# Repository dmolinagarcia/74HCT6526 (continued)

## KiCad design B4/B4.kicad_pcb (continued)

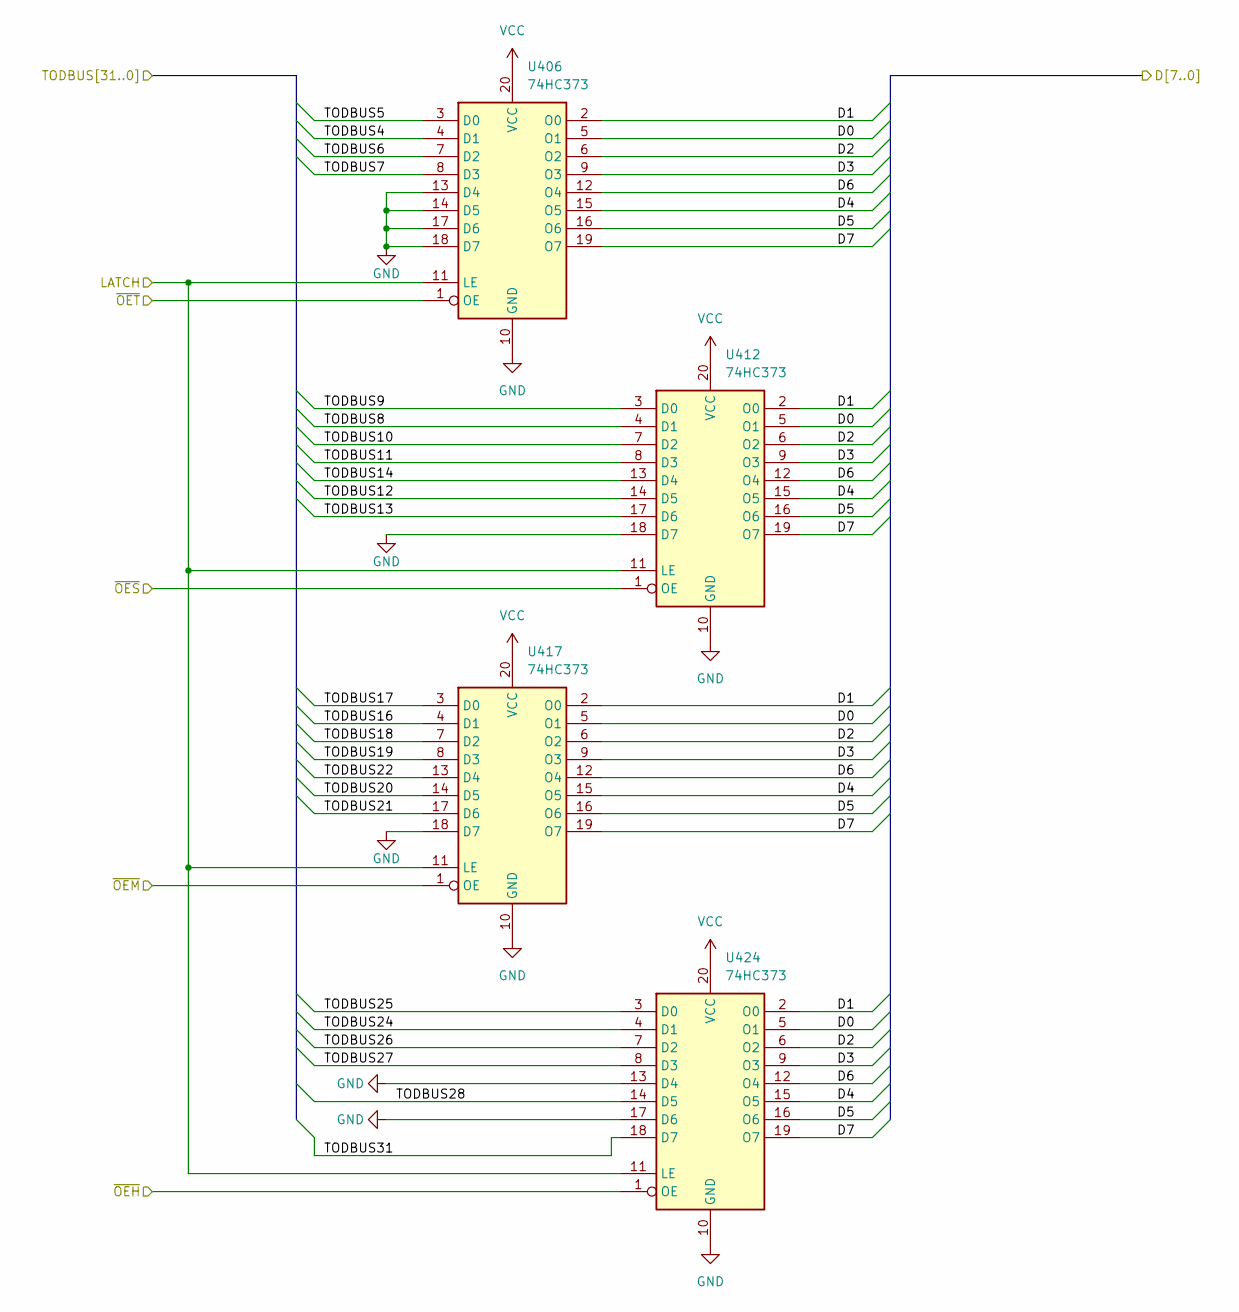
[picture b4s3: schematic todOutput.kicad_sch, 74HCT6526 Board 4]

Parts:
U406, U412, U417, U424: 74HC373; SOIC-20W_7.5x12.8mm_P1.27mm

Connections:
/todComparator/TODBUS4: U406.4 (D1); also elsewhere on the board
/todComparator/TODBUS5: U406.3 (D0); also elsewhere on the board
/todComparator/TODBUS6: U406.7 (D2); also elsewhere on the board
/todComparator/TODBUS7: U406.8 (D3); also elsewhere on the board
/todComparator/TODBUS8: U412.4 (D1); also elsewhere on the board
/todComparator/TODBUS9: U412.3 (D0); also elsewhere on the board
/todComparator/TODBUS10: U412.7 (D2); also elsewhere on the board
/todComparator/TODBUS11: U412.8 (D3); also elsewhere on the board
/todComparator/TODBUS12: U412.14 (D5); also elsewhere on the board
/todComparator/TODBUS13: U412.17 (D6); also elsewhere on the board
/todComparator/TODBUS14: U412.13 (D4); also elsewhere on the board
/todComparator/TODBUS16: U417.4 (D1); also elsewhere on the board
/todComparator/TODBUS17: U417.3 (D0); also elsewhere on the board
/todComparator/TODBUS18: U417.7 (D2); also elsewhere on the board
/todComparator/TODBUS19: U417.8 (D3); also elsewhere on the board
/todComparator/TODBUS20: U417.14 (D5); also elsewhere on the board
/todComparator/TODBUS21: U417.17 (D6); also elsewhere on the board
/todComparator/TODBUS22: U417.13 (D4); also elsewhere on the board
/todComparator/TODBUS24: U424.4 (D1); also elsewhere on the board
/todComparator/TODBUS25: U424.3 (D0); also elsewhere on the board
/todComparator/TODBUS26: U424.7 (D2); also elsewhere on the board
/todComparator/TODBUS27: U424.8 (D3); also elsewhere on the board
/todComparator/TODBUS28: U424.14 (D5); also elsewhere on the board
/todComparator/TODBUS31: U424.18 (D7); also elsewhere on the board
/todControl/LATCH: U406.11 (LE), U412.11 (LE), U417.11 (LE), U424.11 (LE); also elsewhere on the board
/todControl/~OEH: U424.1 (OE); also elsewhere on the board
/todControl/~OEM: U417.1 (OE); also elsewhere on the board
/todControl/~OES: U412.1 (OE); also elsewhere on the board
/todControl/~OET: U406.1 (OE); also elsewhere on the board
D0: U406.5 (O1), U412.5 (O1), U417.5 (O1), U424.5 (O1); also elsewhere on the board
D1: U406.2 (O0), U412.2 (O0), U417.2 (O0), U424.2 (O0); also elsewhere on the board
D2: U406.6 (O2), U412.6 (O2), U417.6 (O2), U424.6 (O2); also elsewhere on the board
D3: U406.9 (O3), U412.9 (O3), U417.9 (O3), U424.9 (O3); also elsewhere on the board
D4: U406.15 (O5), U412.15 (O5), U417.15 (O5), U424.15 (O5); also elsewhere on the board
D5: U406.16 (O6), U412.16 (O6), U417.16 (O6), U424.16 (O6); also elsewhere on the board
D6: U406.12 (O4), U412.12 (O4), U417.12 (O4), U424.12 (O4); also elsewhere on the board
D7: U406.19 (O7), U412.19 (O7), U417.19 (O7), U424.19 (O7); also elsewhere on the board
GND: U406.10 (GND), U406.13 (D4), U406.14 (D5), U406.17 (D6), U406.18 (D7), U412.10 (GND), U412.18 (D7), U417.10 (GND), U417.18 (D7), U424.10 (GND), U424.13 (D4), U424.17 (D6); also elsewhere on the board
VCC: U406.20 (VCC), U412.20 (VCC), U417.20 (VCC), U424.20 (VCC); also elsewhere on the board

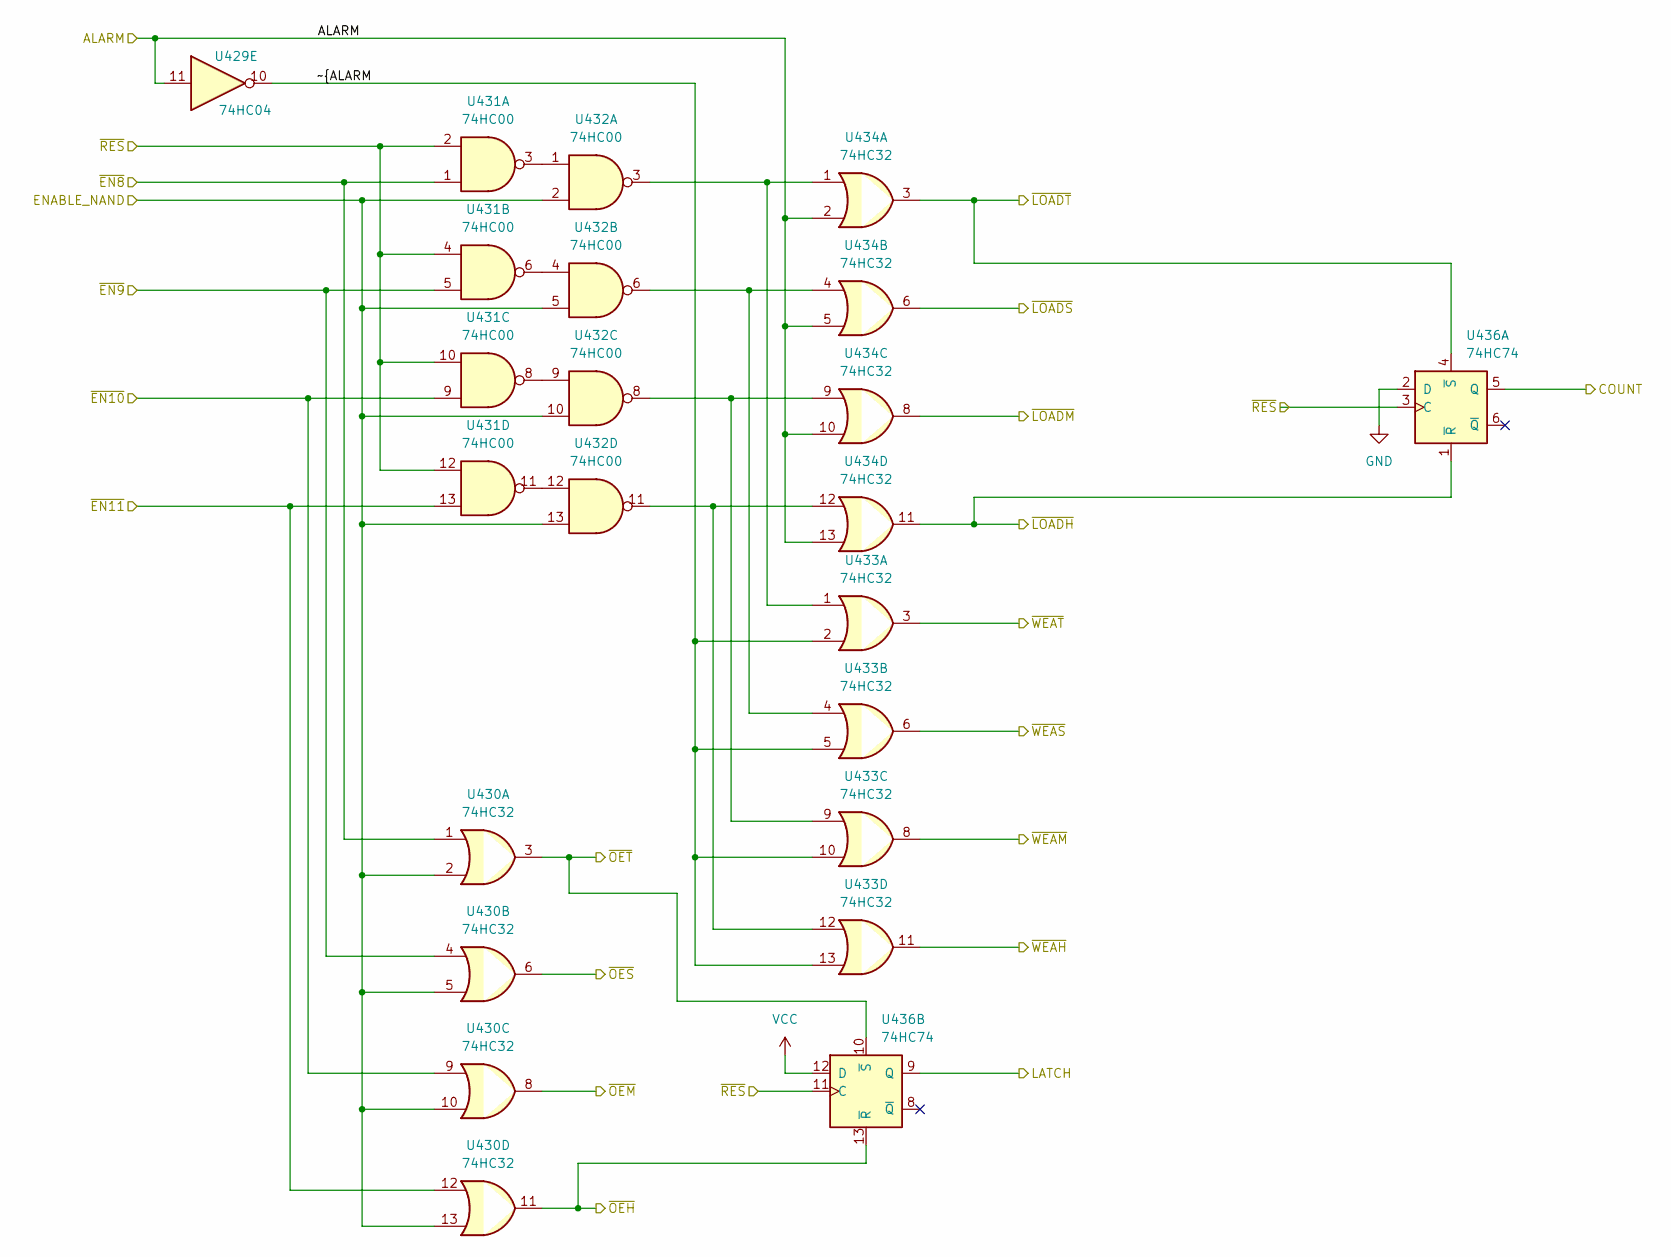
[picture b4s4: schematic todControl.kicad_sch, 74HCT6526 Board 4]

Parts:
U429: 74HC04; SOIC-14_3.9x8.7mm_P1.27mm
U430, U433, U434: 74HC32; SOIC-14_3.9x8.7mm_P1.27mm
U431, U432: 74HC00; SOIC-14_3.9x8.7mm_P1.27mm
U436: 74HC74; SOIC-14_3.9x8.7mm_P1.27mm

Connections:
/todAlarm/~WEAH: U433.11; also elsewhere on the board
/todAlarm/~WEAM: U433.8; also elsewhere on the board
/todAlarm/~WEAS: U433.6; also elsewhere on the board
/todAlarm/~WEAT: U433.3; also elsewhere on the board
/todControl/COUNT: U436.5 (Q); also elsewhere on the board
/todControl/LATCH: U436.9 (Q); also elsewhere on the board
/todControl/~ALARM: U429.10, U433.2, U433.5, U433.10, U433.13
/todControl/~LOADH: U434.11, U436.1 (~R); also elsewhere on the board
/todControl/~LOADM: U434.8; also elsewhere on the board
/todControl/~LOADS: U434.6; also elsewhere on the board
/todControl/~LOADT: U434.3, U436.4 (~S); also elsewhere on the board
/todControl/~OEH: U430.11, U436.13 (~R); also elsewhere on the board
/todControl/~OEM: U430.8; also elsewhere on the board
/todControl/~OES: U430.6; also elsewhere on the board
/todControl/~OET: U430.3, U436.10 (~S); also elsewhere on the board
ALARM: U429.11, U434.2, U434.5, U434.10, U434.13; also elsewhere on the board
ENABLE_NAND: U430.2, U430.5, U430.10, U430.13, U432.2, U432.5, U432.10, U432.13; also elsewhere on the board
GND: U436.2 (D); also elsewhere on the board
unnamed: U431.3, U432.1
unnamed: U431.6, U432.4
unnamed: U431.8, U432.9
unnamed: U431.11, U432.12
unnamed: U432.3, U433.1, U434.1
unnamed: U432.6, U433.4, U434.4
unnamed: U432.8, U433.9, U434.9
unnamed: U432.11, U433.12, U434.12
VCC: U436.12 (D); also elsewhere on the board
~EN8: U430.1, U431.1; also elsewhere on the board
~EN9: U430.4, U431.5; also elsewhere on the board
~EN10: U430.9, U431.9; also elsewhere on the board
~EN11: U430.12, U431.13; also elsewhere on the board
~RES: U431.2, U431.4, U431.10, U431.12, U436.3 (C), U436.11 (C); also elsewhere on the board

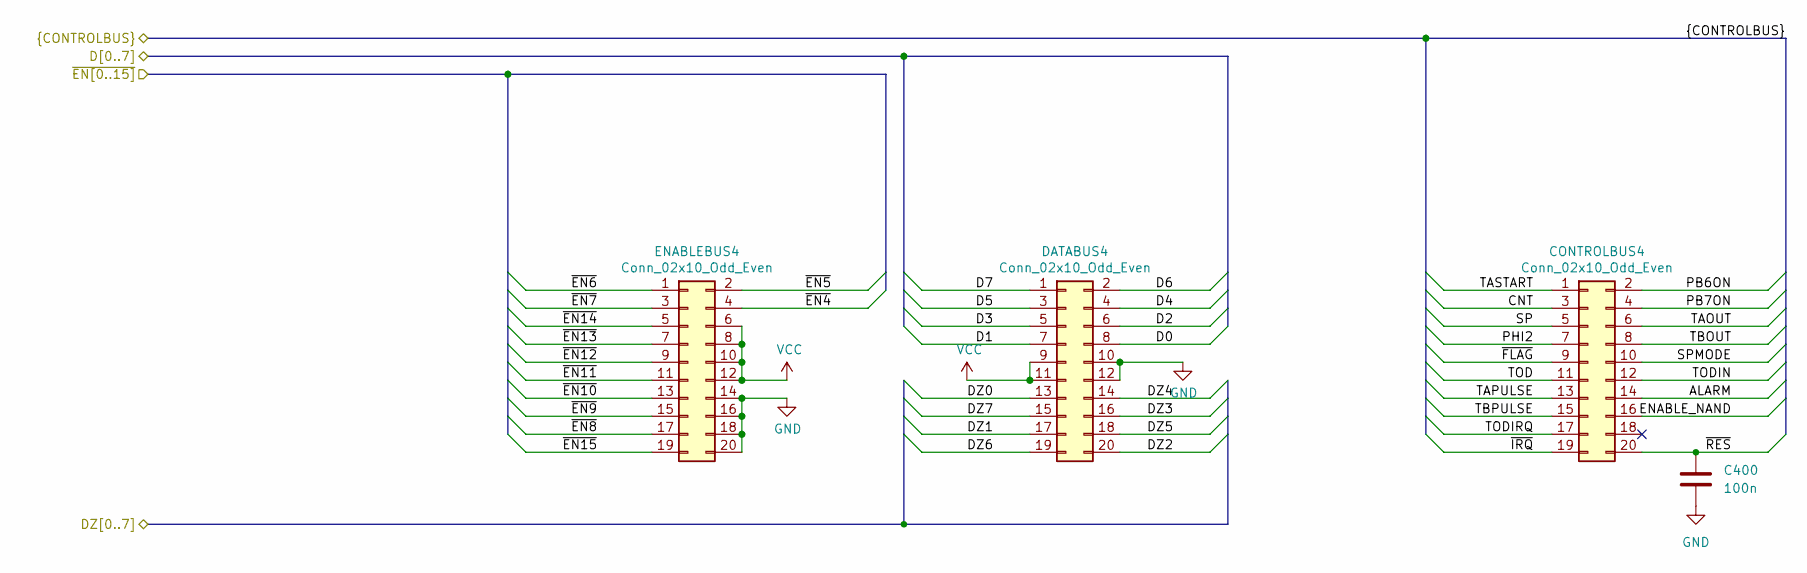
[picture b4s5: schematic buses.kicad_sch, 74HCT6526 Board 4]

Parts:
C400: 100n; C_0603_1608Metric
CONTROLBUS4: Conn_02x10_Odd_Even; PinHeader_2x10_P2.54mm_Vertical
DATABUS4: Conn_02x10_Odd_Even; PinHeader_2x10_P2.54mm_Vertical
ENABLEBUS4: Conn_02x10_Odd_Even; PinHeader_2x10_P2.54mm_Vertical

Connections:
ALARM: CONTROLBUS4.14; also elsewhere on the board
CNT: CONTROLBUS4.3
D0: DATABUS4.8; also elsewhere on the board
D1: DATABUS4.7; also elsewhere on the board
D2: DATABUS4.6; also elsewhere on the board
D3: DATABUS4.5; also elsewhere on the board
D4: DATABUS4.4; also elsewhere on the board
D5: DATABUS4.3; also elsewhere on the board
D6: DATABUS4.2; also elsewhere on the board
D7: DATABUS4.1; also elsewhere on the board
DZ0: DATABUS4.13; also elsewhere on the board
DZ1: DATABUS4.17; also elsewhere on the board
DZ2: DATABUS4.20; also elsewhere on the board
DZ3: DATABUS4.16; also elsewhere on the board
DZ4: DATABUS4.14; also elsewhere on the board
DZ5: DATABUS4.18; also elsewhere on the board
DZ6: DATABUS4.19; also elsewhere on the board
DZ7: DATABUS4.15; also elsewhere on the board
ENABLE_NAND: CONTROLBUS4.16; also elsewhere on the board
GND: C400.2, DATABUS4.10, DATABUS4.12, ENABLEBUS4.14, ENABLEBUS4.16, ENABLEBUS4.18, ENABLEBUS4.20; also elsewhere on the board
PB6ON: CONTROLBUS4.2
PB7ON: CONTROLBUS4.4
PHI2: CONTROLBUS4.7; also elsewhere on the board
SP: CONTROLBUS4.5
SPMODE: CONTROLBUS4.10
TAOUT: CONTROLBUS4.6
TAPULSE: CONTROLBUS4.13
TASTART: CONTROLBUS4.1
TBOUT: CONTROLBUS4.8
TBPULSE: CONTROLBUS4.15
TOD: CONTROLBUS4.11; also elsewhere on the board
TODIN: CONTROLBUS4.12; also elsewhere on the board
TODIRQ: CONTROLBUS4.17; also elsewhere on the board
VCC: DATABUS4.9, DATABUS4.11, ENABLEBUS4.6, ENABLEBUS4.8, ENABLEBUS4.10, ENABLEBUS4.12; also elsewhere on the board
~EN4: ENABLEBUS4.4
~EN5: ENABLEBUS4.2
~EN6: ENABLEBUS4.1
~EN7: ENABLEBUS4.3
~EN8: ENABLEBUS4.17; also elsewhere on the board
~EN9: ENABLEBUS4.15; also elsewhere on the board
~EN10: ENABLEBUS4.13; also elsewhere on the board
~EN11: ENABLEBUS4.11; also elsewhere on the board
~EN12: ENABLEBUS4.9
~EN13: ENABLEBUS4.7
~EN14: ENABLEBUS4.5
~EN15: ENABLEBUS4.19
~FLAG: CONTROLBUS4.9
~IRQ: CONTROLBUS4.19
~RES: C400.1, CONTROLBUS4.20; also elsewhere on the board

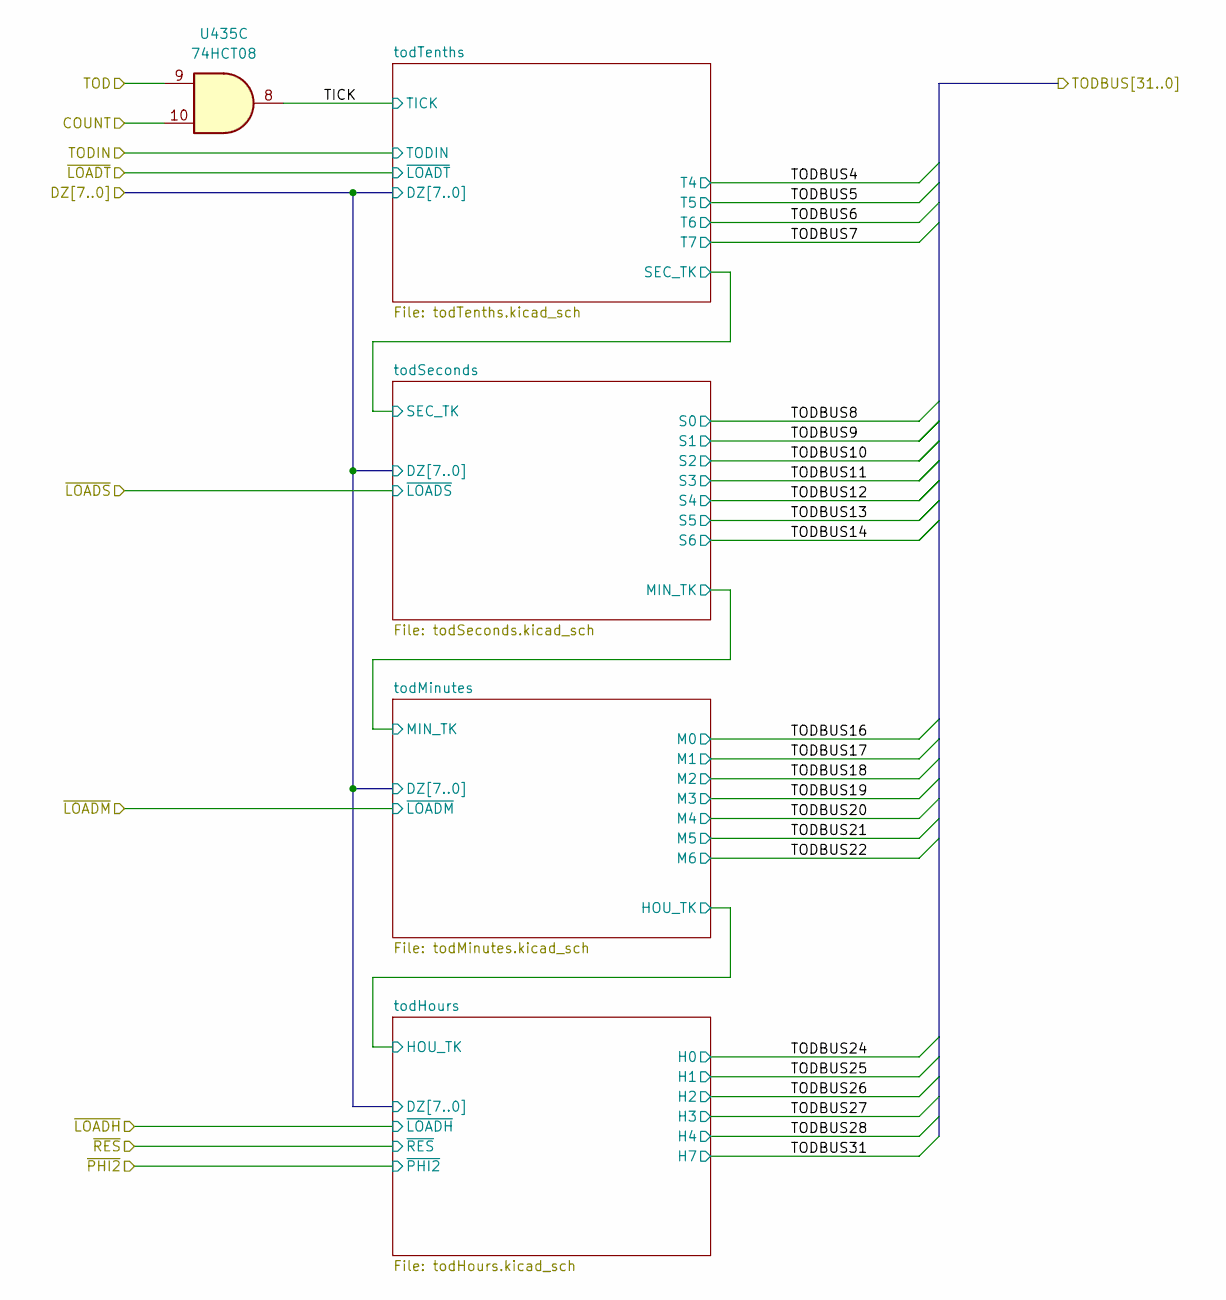
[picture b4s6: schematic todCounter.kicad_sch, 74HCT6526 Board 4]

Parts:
U435: 74HCT08; SOIC-14_3.9x8.7mm_P1.27mm

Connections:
/todControl/COUNT: U435.10; also elsewhere on the board
/todCounter/TICK: U435.8; also elsewhere on the board
TOD: U435.9; also elsewhere on the board

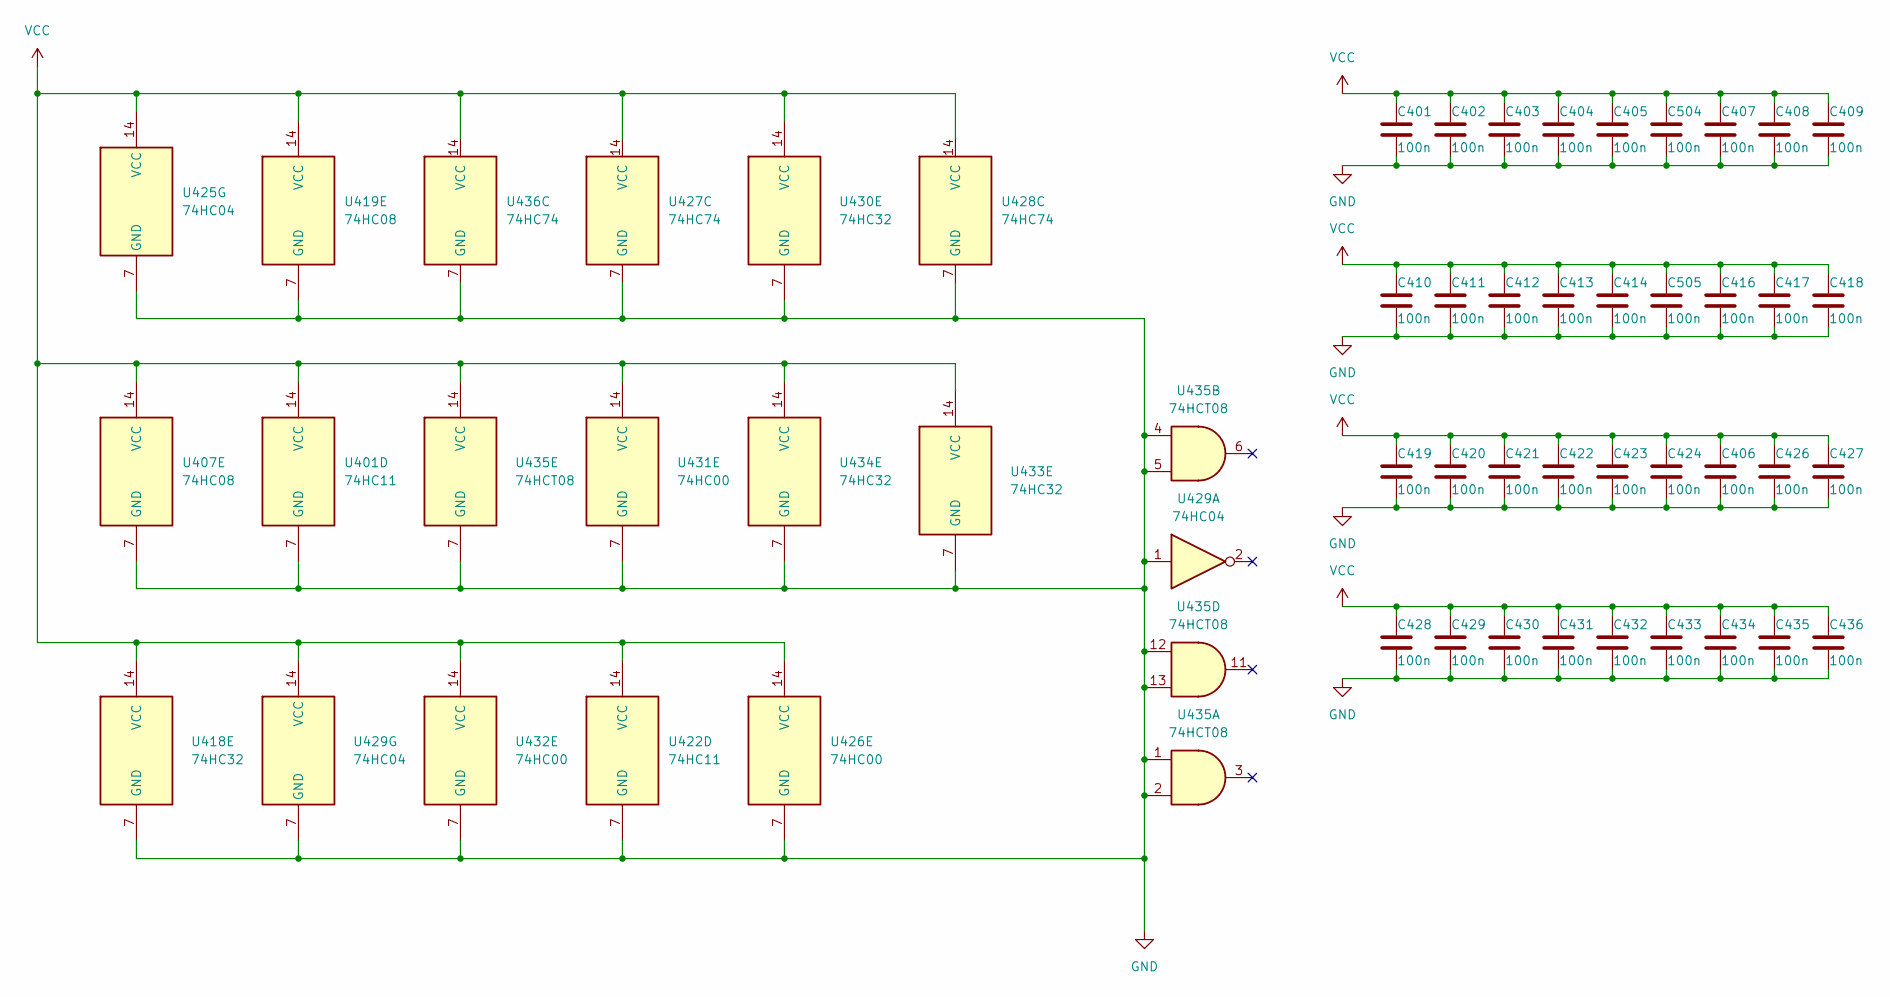
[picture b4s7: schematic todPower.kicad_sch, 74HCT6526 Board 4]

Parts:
C401, C402, C403, C404, C405, C406, C407, C408, C409, C410, C411, C412, C413, C414, C416, C417, C418, C419, C420, C421, C422, C423, C424, C426, C427, C428, C429, C430, C431, C432, C433, C434, C435, C436, C504, C505: 100n; C_0603_1608Metric
U401, U422: 74HC11; SOIC-14_3.9x8.7mm_P1.27mm
U407, U419: 74HC08; SOIC-14_3.9x8.7mm_P1.27mm
U418, U430, U433, U434: 74HC32; SOIC-14_3.9x8.7mm_P1.27mm
U425, U429: 74HC04; SOIC-14_3.9x8.7mm_P1.27mm
U426, U431, U432: 74HC00; SOIC-14_3.9x8.7mm_P1.27mm
U427, U428, U436: 74HC74; SOIC-14_3.9x8.7mm_P1.27mm
U435: 74HCT08; SOIC-14_3.9x8.7mm_P1.27mm

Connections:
GND: C401.2, C402.2, C403.2, C404.2, C405.2, C406.2, C407.2, C408.2, C409.2, C410.2, C411.2, C412.2, C413.2, C414.2, C416.2, C417.2, C418.2, C419.2, C420.2, C421.2, C422.2, C423.2, C424.2, C426.2, C427.2, C428.2, C429.2, C430.2, C431.2, C432.2, C433.2, C434.2, C435.2, C436.2, C504.2, C505.2, U401.7 (GND), U407.7 (GND), U418.7 (GND), U419.7 (GND), U422.7 (GND), U425.7 (GND), U426.7 (GND), U427.7 (GND), U428.7 (GND), U429.1, U429.7 (GND), U430.7 (GND), U431.7 (GND), U432.7 (GND), U433.7 (GND), U434.7 (GND), U435.1, U435.2, U435.4, U435.5, U435.7 (GND), U435.12, U435.13, U436.7 (GND); also elsewhere on the board
VCC: C401.1, C402.1, C403.1, C404.1, C405.1, C406.1, C407.1, C408.1, C409.1, C410.1, C411.1, C412.1, C413.1, C414.1, C416.1, C417.1, C418.1, C419.1, C420.1, C421.1, C422.1, C423.1, C424.1, C426.1, C427.1, C428.1, C429.1, C430.1, C431.1, C432.1, C433.1, C434.1, C435.1, C436.1, C504.1, C505.1, U401.14 (VCC), U407.14 (VCC), U418.14 (VCC), U419.14 (VCC), U422.14 (VCC), U425.14 (VCC), U426.14 (VCC), U427.14 (VCC), U428.14 (VCC), U429.14 (VCC), U430.14 (VCC), U431.14 (VCC), U432.14 (VCC), U433.14 (VCC), U434.14 (VCC), U435.14 (VCC), U436.14 (VCC); also elsewhere on the board

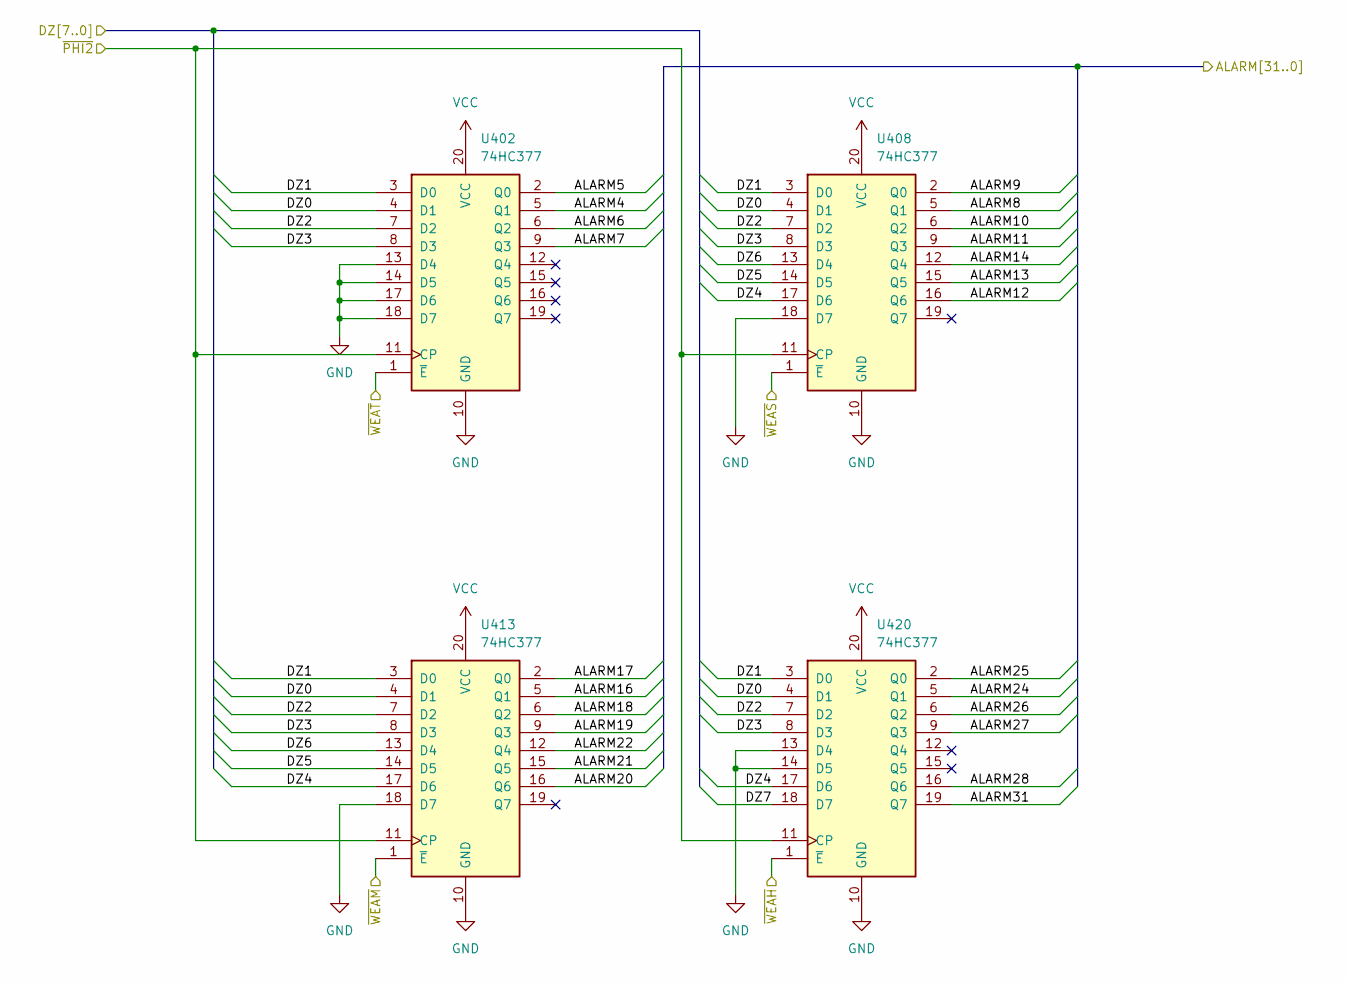
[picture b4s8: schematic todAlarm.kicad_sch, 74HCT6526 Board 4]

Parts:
U402, U408, U413, U420: 74HC377; SOIC-20W_7.5x12.8mm_P1.27mm

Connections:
/todAlarm/ALARM4: U402.5 (Q1); also elsewhere on the board
/todAlarm/ALARM5: U402.2 (Q0); also elsewhere on the board
/todAlarm/ALARM6: U402.6 (Q2); also elsewhere on the board
/todAlarm/ALARM7: U402.9 (Q3); also elsewhere on the board
/todAlarm/ALARM8: U408.5 (Q1); also elsewhere on the board
/todAlarm/ALARM9: U408.2 (Q0); also elsewhere on the board
/todAlarm/ALARM10: U408.6 (Q2); also elsewhere on the board
/todAlarm/ALARM11: U408.9 (Q3); also elsewhere on the board
/todAlarm/ALARM12: U408.16 (Q6); also elsewhere on the board
/todAlarm/ALARM13: U408.15 (Q5); also elsewhere on the board
/todAlarm/ALARM14: U408.12 (Q4); also elsewhere on the board
/todAlarm/ALARM16: U413.5 (Q1); also elsewhere on the board
/todAlarm/ALARM17: U413.2 (Q0); also elsewhere on the board
/todAlarm/ALARM18: U413.6 (Q2); also elsewhere on the board
/todAlarm/ALARM19: U413.9 (Q3); also elsewhere on the board
/todAlarm/ALARM20: U413.16 (Q6); also elsewhere on the board
/todAlarm/ALARM21: U413.15 (Q5); also elsewhere on the board
/todAlarm/ALARM22: U413.12 (Q4); also elsewhere on the board
/todAlarm/ALARM24: U420.5 (Q1); also elsewhere on the board
/todAlarm/ALARM25: U420.2 (Q0); also elsewhere on the board
/todAlarm/ALARM26: U420.6 (Q2); also elsewhere on the board
/todAlarm/ALARM27: U420.9 (Q3); also elsewhere on the board
/todAlarm/ALARM28: U420.16 (Q6); also elsewhere on the board
/todAlarm/ALARM31: U420.19 (Q7); also elsewhere on the board
/todAlarm/~WEAH: U420.1 (~E); also elsewhere on the board
/todAlarm/~WEAM: U413.1 (~E); also elsewhere on the board
/todAlarm/~WEAS: U408.1 (~E); also elsewhere on the board
/todAlarm/~WEAT: U402.1 (~E); also elsewhere on the board
/~PHI2: U402.11 (CP), U408.11 (CP), U413.11 (CP), U420.11 (CP); also elsewhere on the board
DZ0: U402.4 (D1), U408.4 (D1), U413.4 (D1), U420.4 (D1); also elsewhere on the board
DZ1: U402.3 (D0), U408.3 (D0), U413.3 (D0), U420.3 (D0); also elsewhere on the board
DZ2: U402.7 (D2), U408.7 (D2), U413.7 (D2), U420.7 (D2); also elsewhere on the board
DZ3: U402.8 (D3), U408.8 (D3), U413.8 (D3), U420.8 (D3); also elsewhere on the board
DZ4: U408.17 (D6), U413.17 (D6), U420.17 (D6); also elsewhere on the board
DZ5: U408.14 (D5), U413.14 (D5); also elsewhere on the board
DZ6: U408.13 (D4), U413.13 (D4); also elsewhere on the board
DZ7: U420.18 (D7); also elsewhere on the board
GND: U402.10 (GND), U402.13 (D4), U402.14 (D5), U402.17 (D6), U402.18 (D7), U408.10 (GND), U408.18 (D7), U413.10 (GND), U413.18 (D7), U420.10 (GND), U420.13 (D4), U420.14 (D5); also elsewhere on the board
VCC: U402.20 (VCC), U408.20 (VCC), U413.20 (VCC), U420.20 (VCC); also elsewhere on the board

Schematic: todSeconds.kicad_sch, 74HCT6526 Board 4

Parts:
U407: 74HC08; SOIC-14_3.9x8.7mm_P1.27mm
U409, U410: 74HC193; SOIC-16_3.9x9.9mm_P1.27mm

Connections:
/todComparator/TODBUS8: U410.3 (QA); also elsewhere on the board
/todComparator/TODBUS9: U407.13, U410.2 (QB); also elsewhere on the board
/todComparator/TODBUS10: U410.6 (QC); also elsewhere on the board
/todComparator/TODBUS11: U407.12, U410.7 (QD); also elsewhere on the board
/todComparator/TODBUS12: U409.3 (QA); also elsewhere on the board
/todComparator/TODBUS13: U407.1, U409.2 (QB); also elsewhere on the board
/todComparator/TODBUS14: U407.2, U409.6 (QC); also elsewhere on the board
/todControl/~LOADS: U409.11 (~LOAD), U410.11 (~LOAD); also elsewhere on the board
/todCounter/todMinutes/MIN_TK: U407.3, U409.14 (CLR); also elsewhere on the board
/todCounter/todSeconds/SEC_TK: U410.5 (UP); also elsewhere on the board
DZ0: U410.15 (A); also elsewhere on the board
DZ1: U410.1 (B); also elsewhere on the board
DZ2: U410.10 (C); also elsewhere on the board
DZ3: U410.9 (D); also elsewhere on the board
DZ4: U409.15 (A); also elsewhere on the board
DZ5: U409.1 (B); also elsewhere on the board
DZ6: U409.10 (C); also elsewhere on the board
GND: U409.8 (GND), U409.9 (D), U410.8 (GND); also elsewhere on the board
unnamed: U407.11, U409.5 (UP), U410.14 (CLR)
VCC: U409.4 (DOWN), U409.16 (VCC), U410.4 (DOWN), U410.16 (VCC); also elsewhere on the board

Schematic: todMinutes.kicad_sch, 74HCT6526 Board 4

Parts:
U407: 74HC08; SOIC-14_3.9x8.7mm_P1.27mm
U414, U415: 74HC193; SOIC-16_3.9x9.9mm_P1.27mm

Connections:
/todComparator/TODBUS16: U415.3 (QA); also elsewhere on the board
/todComparator/TODBUS17: U407.4, U415.2 (QB); also elsewhere on the board
/todComparator/TODBUS18: U415.6 (QC); also elsewhere on the board
/todComparator/TODBUS19: U407.5, U415.7 (QD); also elsewhere on the board
/todComparator/TODBUS20: U414.3 (QA); also elsewhere on the board
/todComparator/TODBUS21: U407.10, U414.2 (QB); also elsewhere on the board
/todComparator/TODBUS22: U407.9, U414.6 (QC); also elsewhere on the board
/todControl/~LOADM: U414.11 (~LOAD), U415.11 (~LOAD); also elsewhere on the board
/todCounter/todHours/HOU_TK: U407.8, U414.14 (CLR); also elsewhere on the board
/todCounter/todMinutes/MIN_TK: U415.5 (UP); also elsewhere on the board
DZ0: U415.15 (A); also elsewhere on the board
DZ1: U415.1 (B); also elsewhere on the board
DZ2: U415.10 (C); also elsewhere on the board
DZ3: U415.9 (D); also elsewhere on the board
DZ4: U414.15 (A); also elsewhere on the board
DZ5: U414.1 (B); also elsewhere on the board
DZ6: U414.10 (C); also elsewhere on the board
GND: U414.8 (GND), U414.9 (D), U415.8 (GND); also elsewhere on the board
unnamed: U407.6, U414.5 (UP), U415.14 (CLR)
VCC: U414.4 (DOWN), U414.16 (VCC), U415.4 (DOWN), U415.16 (VCC); also elsewhere on the board

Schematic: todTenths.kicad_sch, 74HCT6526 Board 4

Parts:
U401: 74HC11; SOIC-14_3.9x8.7mm_P1.27mm
U403, U404: 74HC193; SOIC-16_3.9x9.9mm_P1.27mm
U418: 74HC32; SOIC-14_3.9x8.7mm_P1.27mm
U429: 74HC04; SOIC-14_3.9x8.7mm_P1.27mm

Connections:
/todComparator/TODBUS4: U404.3 (QA); also elsewhere on the board
/todComparator/TODBUS5: U401.3, U401.4, U404.2 (QB); also elsewhere on the board
/todComparator/TODBUS6: U404.6 (QC); also elsewhere on the board
/todComparator/TODBUS7: U401.5, U404.7 (QD); also elsewhere on the board
/todControl/~LOADT: U403.11 (~LOAD), U404.11 (~LOAD); also elsewhere on the board
/todCounter/TICK: U403.5 (UP); also elsewhere on the board
/todCounter/todSeconds/SEC_TK: U401.6, U404.14 (CLR); also elsewhere on the board
/todCounter/todTenths/TODBUS0: U401.10, U403.3 (QA)
/todCounter/todTenths/TODBUS1: U401.13, U403.2 (QB)
/todCounter/todTenths/TODBUS2: U401.2, U401.9, U403.6 (QC)
DZ0: U404.15 (A); also elsewhere on the board
DZ1: U404.1 (B); also elsewhere on the board
DZ2: U404.10 (C); also elsewhere on the board
DZ3: U404.9 (D); also elsewhere on the board
GND: U403.1 (B), U403.8 (GND), U403.9 (D), U403.10 (C), U403.15 (A), U404.8 (GND); also elsewhere on the board
unnamed: U401.1, U429.6
unnamed: U401.8, U418.2
unnamed: U401.12, U418.1
unnamed: U403.14 (CLR), U404.5 (UP), U418.3
TODIN: U401.11, U429.5; also elsewhere on the board
VCC: U403.4 (DOWN), U403.16 (VCC), U404.4 (DOWN), U404.16 (VCC); also elsewhere on the board

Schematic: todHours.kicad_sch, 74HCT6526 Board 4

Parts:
U418: 74HC32; SOIC-14_3.9x8.7mm_P1.27mm
U419: 74HC08; SOIC-14_3.9x8.7mm_P1.27mm
U421: 74HC193; SOIC-16_3.9x9.9mm_P1.27mm
U422: 74HC11; SOIC-14_3.9x8.7mm_P1.27mm
U425, U429: 74HC04; SOIC-14_3.9x8.7mm_P1.27mm
U426: 74HC00; SOIC-14_3.9x8.7mm_P1.27mm
U427, U428: 74HC74; SOIC-14_3.9x8.7mm_P1.27mm

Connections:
/todComparator/TODBUS24: U421.3 (QA), U422.4; also elsewhere on the board
/todComparator/TODBUS25: U421.2 (QB), U422.1, U422.5, U422.11; also elsewhere on the board
/todComparator/TODBUS26: U421.6 (QC); also elsewhere on the board
/todComparator/TODBUS27: U421.7 (QD), U422.2, U425.11; also elsewhere on the board
/todComparator/TODBUS28: U422.3, U422.10, U427.5 (Q); also elsewhere on the board
/todComparator/TODBUS31: U427.9 (Q); also elsewhere on the board
/todControl/~LOADH: U418.4, U419.13; also elsewhere on the board
/todCounter/todHours/H4_FLIP: U418.8, U427.3 (C)
/todCounter/todHours/H7_FLIP: U427.11 (C), U428.9 (Q)
/todCounter/todHours/HOU_TK: U421.5 (UP); also elsewhere on the board
/todCounter/todHours/~H4: U422.13, U427.2 (D), U427.6 (~Q)
/~PHI2: U428.3 (C), U428.11 (C); also elsewhere on the board
DZ0: U418.13; also elsewhere on the board
DZ1: U419.2; also elsewhere on the board
DZ2: U419.4; also elsewhere on the board
DZ3: U419.10; also elsewhere on the board
DZ4: U425.5, U426.5; also elsewhere on the board
DZ7: U425.9, U426.9; also elsewhere on the board
GND: U421.8 (GND), U428.12 (D); also elsewhere on the board
unnamed: U418.5, U425.2
unnamed: U418.9, U421.14 (CLR), U422.12
unnamed: U418.10, U422.6, U425.13
unnamed: U418.11, U421.15 (A)
unnamed: U418.6, U418.12, U425.3
unnamed: U419.1, U419.5, U419.9, U425.4, U426.1, U426.4, U426.10, U426.13
unnamed: U419.3, U421.1 (B)
unnamed: U419.6, U421.10 (C)
unnamed: U419.8, U421.9 (D)
unnamed: U419.11, U421.11 (~LOAD)
unnamed: U419.12, U428.5 (Q)
unnamed: U422.8, U429.3
unnamed: U422.9, U425.10
unnamed: U425.6, U426.2
unnamed: U425.8, U426.12
unnamed: U425.12, U428.1 (~R)
unnamed: U426.3, U427.1 (~R)
unnamed: U426.6, U427.4 (~S)
unnamed: U426.8, U427.10 (~S)
unnamed: U426.11, U427.13 (~R)
unnamed: U427.8 (~Q), U427.12 (D)
unnamed: U428.13 (~R), U429.4
VCC: U421.4 (DOWN), U421.16 (VCC), U428.2 (D), U428.4 (~S), U428.10 (~S); also elsewhere on the board
~RES: U425.1; also elsewhere on the board

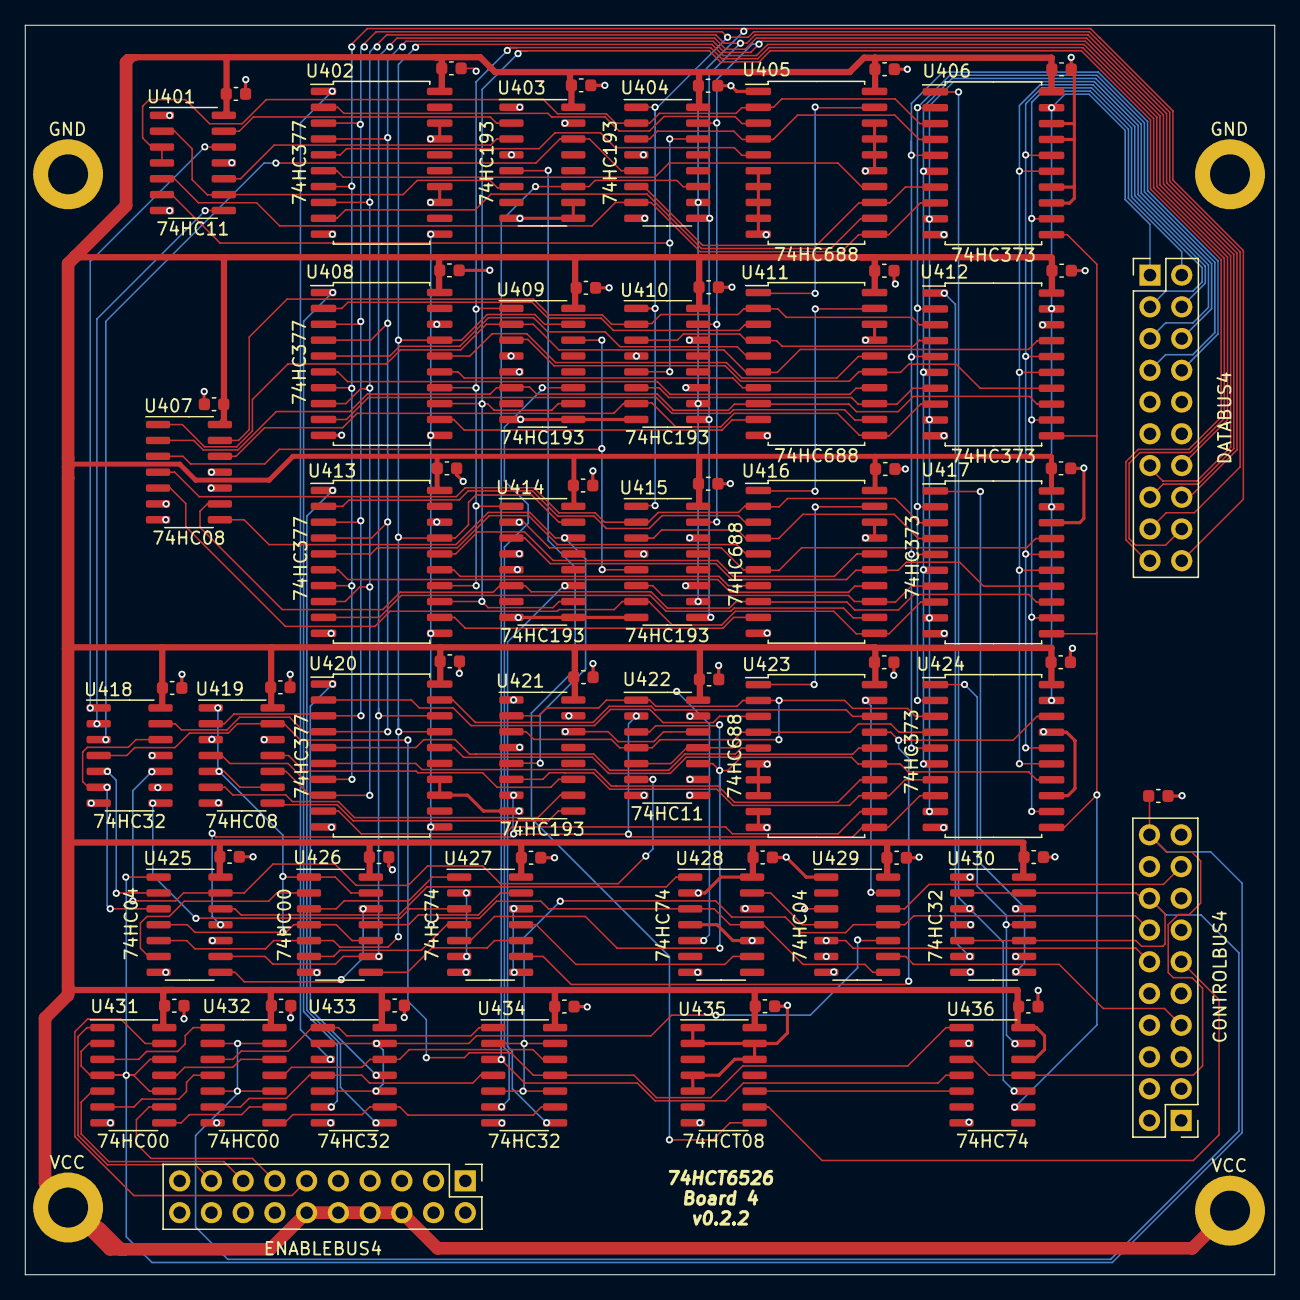
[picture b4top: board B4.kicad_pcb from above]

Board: 4 copper layers, 100.0 x 100.0 mm, 80 parts (0 on the bottom side), 143 nets.

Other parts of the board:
GND101, GND102: GND; MountingHole_2.2mm_M2_DIN965_Pad
VCC101, VCC102: VCC; MountingHole_2.2mm_M2_DIN965_Pad

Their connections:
GND: GND101.GND, GND102.GND; also elsewhere on the board
VCC: VCC101.VCC, VCC102.VCC; also elsewhere on the board
